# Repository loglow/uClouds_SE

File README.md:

# µClouds SE (uClouds, microClouds) Eurorack [Rev D]

## 8HP Eurorack module | Granular audio processor

[μClouds SE](http://uclouds-se.com) is a granular audio processor that creates textures and soundscapes by combining multiple segments of sound taken from a recording buffer.

This re-engineered Eurorack module updates and simplifies the classic [Mutable Instruments Clouds](https://mutable-instruments.net/modules/clouds/) design by miniaturizing the module from 18HP to 8HP and redesigning the front panel layout without eliminating any original functionality.

Fully compatible with upstream Clouds firmware. Includes power cable, mounting hardware, and a one-year warranty. Designed and built with care by [Tall Dog Electronics](http://tall-dog.com) in Western Massachusetts. Licensed [CC BY-SA 4.0](https://creativecommons.org/licenses/by-sa/4.0/) open source hardware.

- **Height:** 3U (128.5 mm)
- **Width:** 8HP (40.3 mm)
- **Depth:** 43 mm (with power)
- **+12V:** 120 mA (average)
- **-12V:** 10 mA (average)

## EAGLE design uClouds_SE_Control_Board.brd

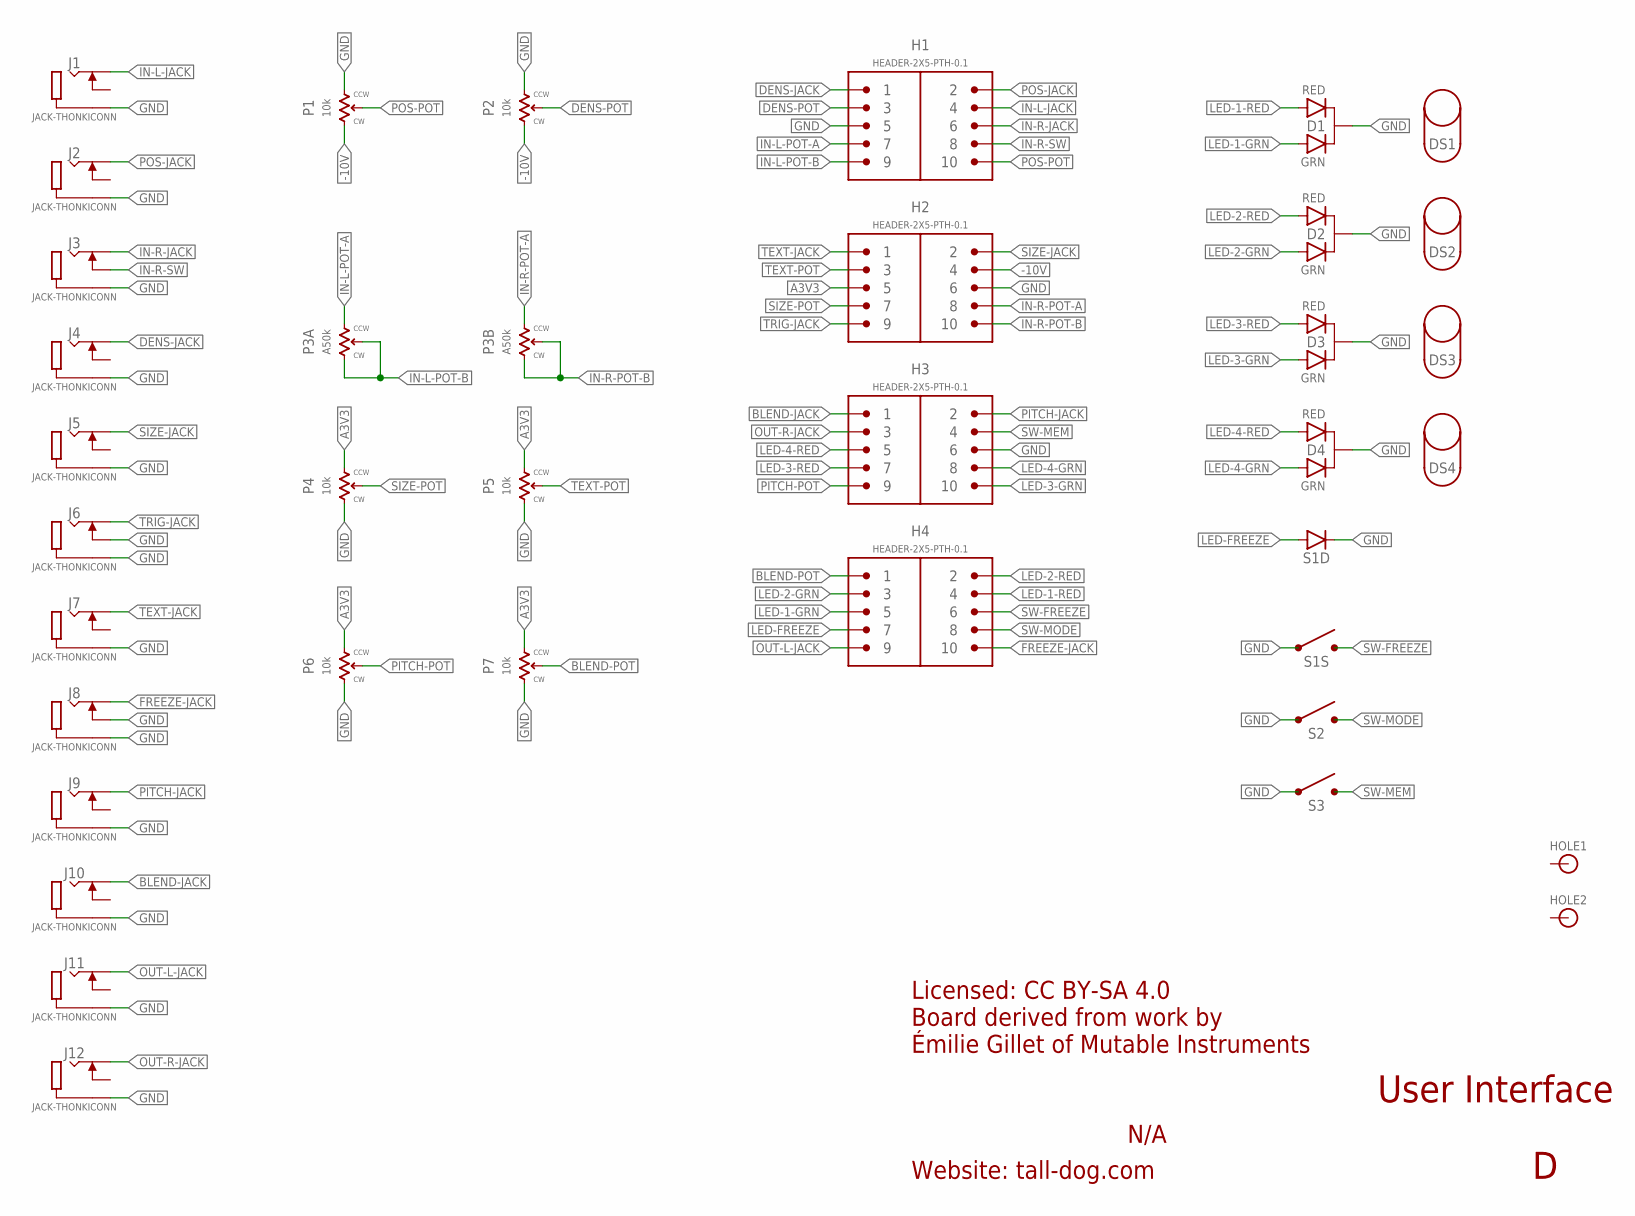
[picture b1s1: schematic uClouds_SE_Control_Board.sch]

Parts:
D1, D2, D3, D4: LED-DUAL-PTH; LED-T1-3
DS1, DS2, DS3, DS4: LED-SPACER
H1, H2, H3, H4: HEADER-2X5-PTH-0.1; PTH-0.1-2X5-MALE
HOLE1, HOLE2: HOLE; M2.5-HOLE
J1, J2, J3, J4, J5, J6, J7, J8, J9, J10, J11, J12: JACK-THONKICONN; THONKICONN
P1, P2, P4, P5, P6, P7: 10k; POT-R0904N
P3: A50k; POT-RK1109G
S1: SPST-LED; TL1265
S2, S3: SPST-PTH; TL1105

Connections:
-10V: H2.4, P1.P$3 (3), P2.P$3 (3)
A3V3: H2.5, P4.P$1 (1), P5.P$1 (1), P6.P$1 (1), P7.P$1 (1)
BLEND-JACK: H3.1, J10.P3 (3)
BLEND-POT: H4.1, P7.P$2 (2)
DENS-JACK: H1.1, J4.P3 (3)
DENS-POT: H1.3, P2.P$2 (2)
FREEZE-JACK: H4.10, J8.P3 (3)
GND: D1.2 (C), D2.2 (C), D3.2 (C), D4.2 (C), H1.5, H2.6, H3.6, J1.P1 (1), J2.P1 (1), J3.P1 (1), J4.P1 (1), J5.P1 (1), J6.P1 (1), J6.P2 (2), J7.P1 (1), J8.P1 (1), J8.P2 (2), J9.P1 (1), J10.P1 (1), J11.P1 (1), J12.P1 (1), P1.P$1 (1), P2.P$1 (1), P4.P$3 (3), P5.P$3 (3), P6.P$3 (3), P7.P$3 (3), S1.1, S1.2 (1), S1.5 (C), S2.1, S2.2 (1), S3.1, S3.2 (1)
IN-L-JACK: H1.4, J1.P3 (3)
IN-L-POT-A: H1.7, P3.1
IN-L-POT-B: H1.9, P3.2, P3.3
IN-R-JACK: H1.6, J3.P3 (3)
IN-R-POT-A: H2.8, P3.1' (1)
IN-R-POT-B: H2.10, P3.2' (2), P3.3' (3)
IN-R-SW: H1.8, J3.P2 (2)
LED-1-GRN: D1.3 (GRN), H4.5
LED-1-RED: D1.1 (RED), H4.4
LED-2-GRN: D2.3 (GRN), H4.3
LED-2-RED: D2.1 (RED), H4.2
LED-3-GRN: D3.3 (GRN), H3.10
LED-3-RED: D3.1 (RED), H3.7
LED-4-GRN: D4.3 (GRN), H3.8
LED-4-RED: D4.1 (RED), H3.5
LED-FREEZE: H4.7, S1.6 (A)
OUT-L-JACK: H4.9, J11.P3 (3)
OUT-R-JACK: H3.3, J12.P3 (3)
PITCH-JACK: H3.2, J9.P3 (3)
PITCH-POT: H3.9, P6.P$2 (2)
POS-JACK: H1.2, J2.P3 (3)
POS-POT: H1.10, P1.P$2 (2)
SIZE-JACK: H2.2, J5.P3 (3)
SIZE-POT: H2.7, P4.P$2 (2)
SW-FREEZE: H4.6, S1.3 (2), S1.4 (2)
SW-MEM: H3.4, S3.3 (2), S3.4 (2)
SW-MODE: H4.8, S2.3 (2), S2.4 (2)
TEXT-JACK: H2.1, J7.P3 (3)
TEXT-POT: H2.3, P5.P$2 (2)
TRIG-JACK: H2.9, J6.P3 (3)

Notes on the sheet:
Licensed: CC BY-SA 4.0 Board derived from work by Émilie Gillet of Mutable Instruments
Website: tall-dog.com
N/A
User Interface

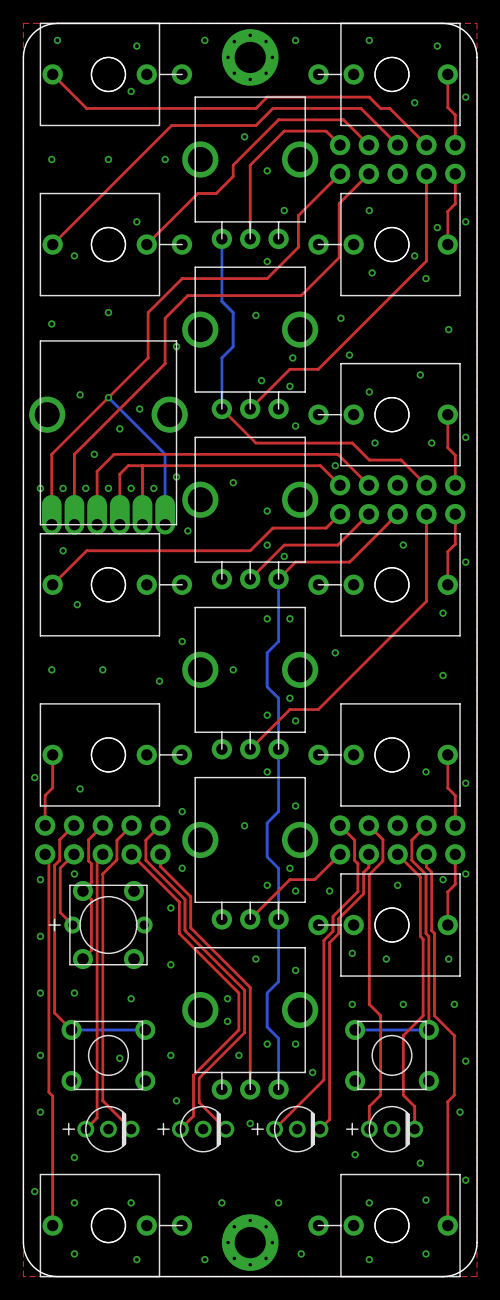
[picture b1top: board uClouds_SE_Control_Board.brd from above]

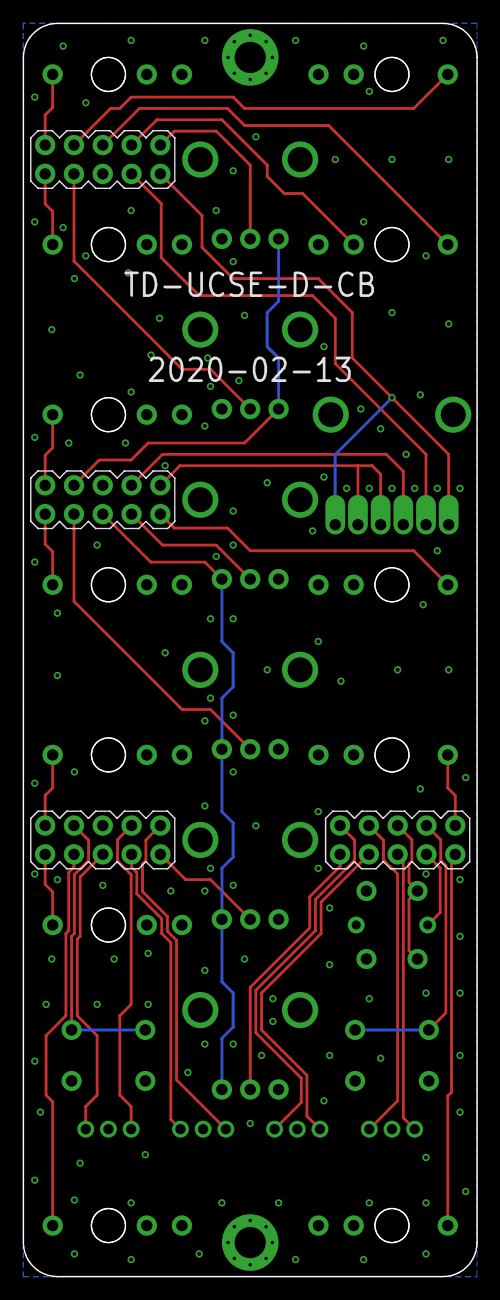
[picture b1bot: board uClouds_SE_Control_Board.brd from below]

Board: 2 copper layers, 40.0 x 110.5 mm, 36 parts (4 on the bottom side), 38 nets.

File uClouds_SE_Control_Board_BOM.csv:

Reference,Quantity,Description,Manufacturer,Part Number,Digi-Key P/N
D1 D2 D3 D4,4,LED GRN/RED DIFF 3MM ROUND T/H,Kingbright,WP3VEGW,754-1221-ND
DS1 DS2 DS3 DS4,4,LED SPACER 3MM T-1 BLACK 8MM,Essentra,LEDM-2-08,RPC4261-ND
H1 H2 H3 H4,4,CONN HEADER 10POS .100 STR 15AU,Amphenol FCI,67997-210HLF,609-3236-ND
J1 J2 J3 J4 J5 J6 J7 J8 J9 J10 J11 J12,12,3.5MM JACK VERTICAL PCB MOUNT,Wenzhou QingPu,WQP-PJ398SM,N/A
P1 P2 P4 P5 P6 P7,6,POT 9MM LINEAR B10K,Song Huei,"R0904N-B10K,L-25KQ/LWS",N/A
P3,1,POT 9MM AUDIO A50K DUAL GANG,Song Huei,"RK1109G-A50K,L-25KC",N/A
S1,1,SWITCH TACTILE SPST-NO 0.05A 12V,E-Switch,TL1265GQSCLR,EG4967-ND
S2 S3,2,SWITCH TACTILE SPST-NO 0.05A 12V,E-Switch,TL1105DF160Q,EG1865-ND

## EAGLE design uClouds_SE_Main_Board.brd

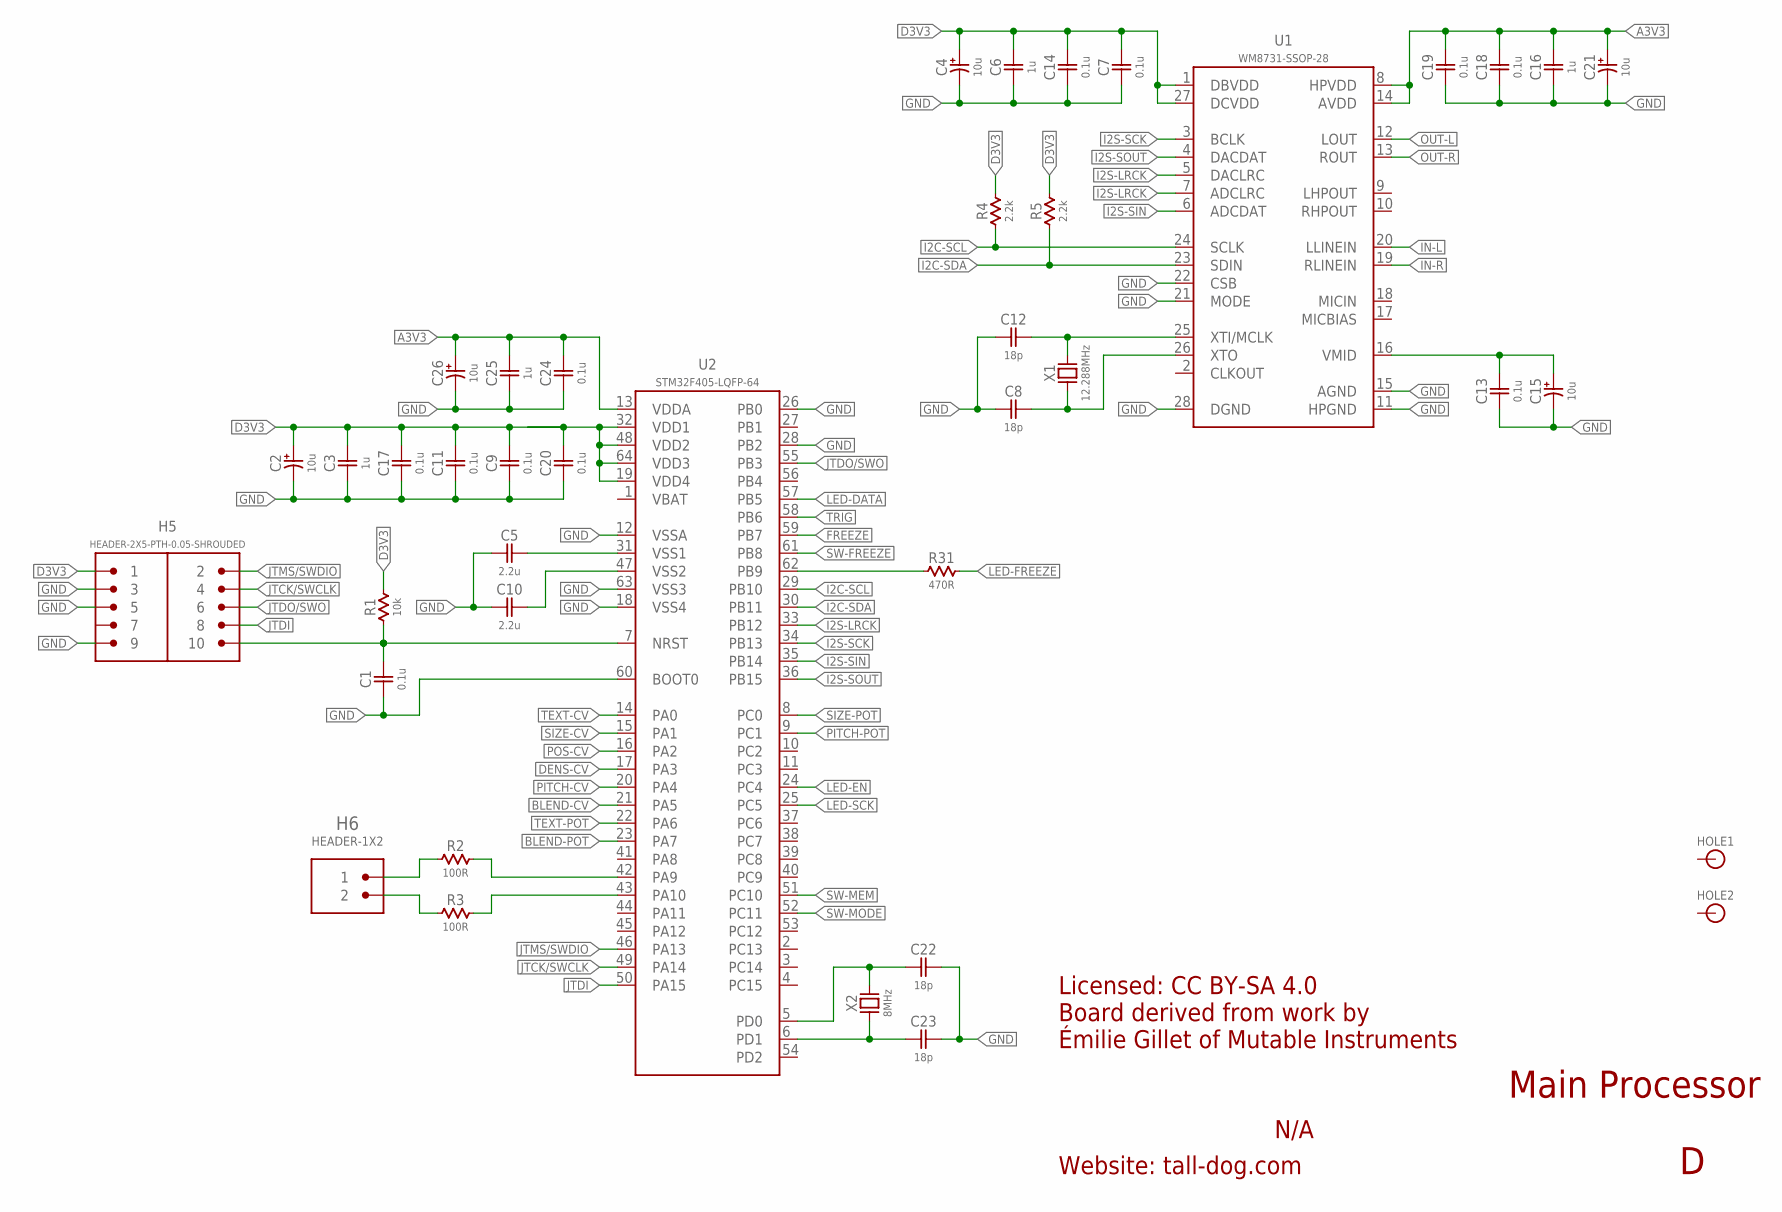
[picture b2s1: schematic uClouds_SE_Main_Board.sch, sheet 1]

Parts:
C1, C7, C9, C11, C13, C14, C17, C18, C19, C20, C24: 0.1u; 0603-NP
C2, C4, C15, C21, C26: 10u; ELECTRO-SMD-4.3MM
C3, C6, C16, C25: 1u; 0603-NP
C5, C10: 2.2u; 0603-NP
C8, C12, C22, C23: 18p; 0603-NP
H5: HEADER-2X5-PTH-0.05-SHROUDED; PTH-0.05-2X5-SHROUDED
H6: HEADER-1X2; PTH-0.1-1X2
HOLE1, HOLE2: HOLE; M2.5-HOLE
R1: 10k; 0603-NP
R2, R3: 100R; 0603-NP
R4, R5: 2.2k; 0603-NP
R31: 470R; 0603-NP
U1: WM8731-SSOP-28; SSOP-28
U2: STM32F405-LQFP-64; LQFP-64
X1: 12.288MHz; CRYSTAL-ABM3
X2: 8MHz; CRYSTAL-ABM3

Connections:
A3V3: C16.2, C18.2, C19.2, C21.A (POS), C24.2, C25.2, C26.A (POS), U1.8 (HPVDD), U1.14 (AVDD), U2.13 (VDDA); also elsewhere on the board
BLEND-CV: U2.21 (PA5); also elsewhere on the board
BLEND-POT: U2.23 (PA7); also elsewhere on the board
D3V3: C2.A (POS), C3.2, C4.A (POS), C6.2, C7.2, C9.2, C11.2, C14.2, C17.2, C20.2, H5.1, R1.2, R4.2, R5.2, U1.1 (DBVDD), U1.27 (DCVDD), U2.19 (VDD4), U2.32 (VDD1), U2.48 (VDD2), U2.64 (VDD3); also elsewhere on the board
DENS-CV: U2.17 (PA3); also elsewhere on the board
FREEZE: U2.59 (PB7); also elsewhere on the board
GND: C1.1, C2.C (NEG), C3.1, C4.C (NEG), C5.1, C6.1, C7.1, C8.1, C9.1, C10.1, C11.1, C12.1, C13.1, C14.1, C15.C (NEG), C16.1, C17.1, C18.1, C19.1, C20.1, C21.C (NEG), C22.2, C23.2, C24.1, C25.1, C26.C (NEG), H5.3, H5.5, H5.9, U1.11 (HPGND), U1.15 (AGND), U1.21 (MODE), U1.22 (CSB), U1.28 (DGND), U2.12 (VSSA), U2.18 (VSS4), U2.26 (PB0), U2.28 (PB2), U2.60 (BOOT0), U2.63 (VSS3); also elsewhere on the board
I2C-SCL: R4.1, U1.24 (SCLK), U2.29 (PB10)
I2C-SDA: R5.1, U1.23 (SDIN), U2.30 (PB11)
I2S-LRCK: U1.5 (DACLRC), U1.7 (ADCLRC), U2.33 (PB12)
I2S-SCK: U1.3 (BCLK), U2.34 (PB13)
I2S-SIN: U1.6 (ADCDAT), U2.35 (PB14)
I2S-SOUT: U1.4 (DACDAT), U2.36 (PB15)
IN-L: U1.20 (LLINEIN); also elsewhere on the board
IN-R: U1.19 (RLINEIN); also elsewhere on the board
JTCK/SWCLK: H5.4, U2.49 (PA14)
JTDI: H5.8, U2.50 (PA15)
JTDO/SWO: H5.6, U2.55 (PB3)
JTMS/SWDIO: H5.2, U2.46 (PA13)
LED-DATA: U2.57 (PB5); also elsewhere on the board
LED-EN: U2.24 (PC4); also elsewhere on the board
LED-FREEZE: R31.2; also elsewhere on the board
LED-SCK: U2.25 (PC5); also elsewhere on the board
unnamed: C5.2, U2.31 (VSS1)
unnamed: C10.2, U2.47 (VSS2)
unnamed: C22.1, U2.5 (PD0), X2.2
unnamed: C23.1, U2.6 (PD1), X2.1
unnamed: C12.2, U1.25 (XTI/MCLK), X1.2
unnamed: C8.2, U1.26 (XTO), X1.1
unnamed: C13.2, C15.A (POS), U1.16 (VMID)
unnamed: R31.1, U2.62 (PB9)
OUT-L: U1.12 (LOUT); also elsewhere on the board
OUT-R: U1.13 (ROUT); also elsewhere on the board
PITCH-CV: U2.20 (PA4); also elsewhere on the board
PITCH-POT: U2.9 (PC1); also elsewhere on the board
POS-CV: U2.16 (PA2); also elsewhere on the board
RESET: C1.2, H5.10, R1.1, U2.7 (NRST)
RX: H6.2, R3.1
RX1: R3.2, U2.43 (PA10)
SIZE-CV: U2.15 (PA1); also elsewhere on the board
SIZE-POT: U2.8 (PC0); also elsewhere on the board
SW-FREEZE: U2.61 (PB8); also elsewhere on the board
SW-MEM: U2.51 (PC10); also elsewhere on the board
SW-MODE: U2.52 (PC11); also elsewhere on the board
TEXT-CV: U2.14 (PA0); also elsewhere on the board
TEXT-POT: U2.22 (PA6); also elsewhere on the board
TRIG: U2.58 (PB6); also elsewhere on the board
TX: H6.1, R2.1
TX1: R2.2, U2.42 (PA9)

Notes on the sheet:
Licensed: CC BY-SA 4.0 Board derived from work by Émilie Gillet of Mutable Instruments
Website: tall-dog.com
N/A
Main Processor

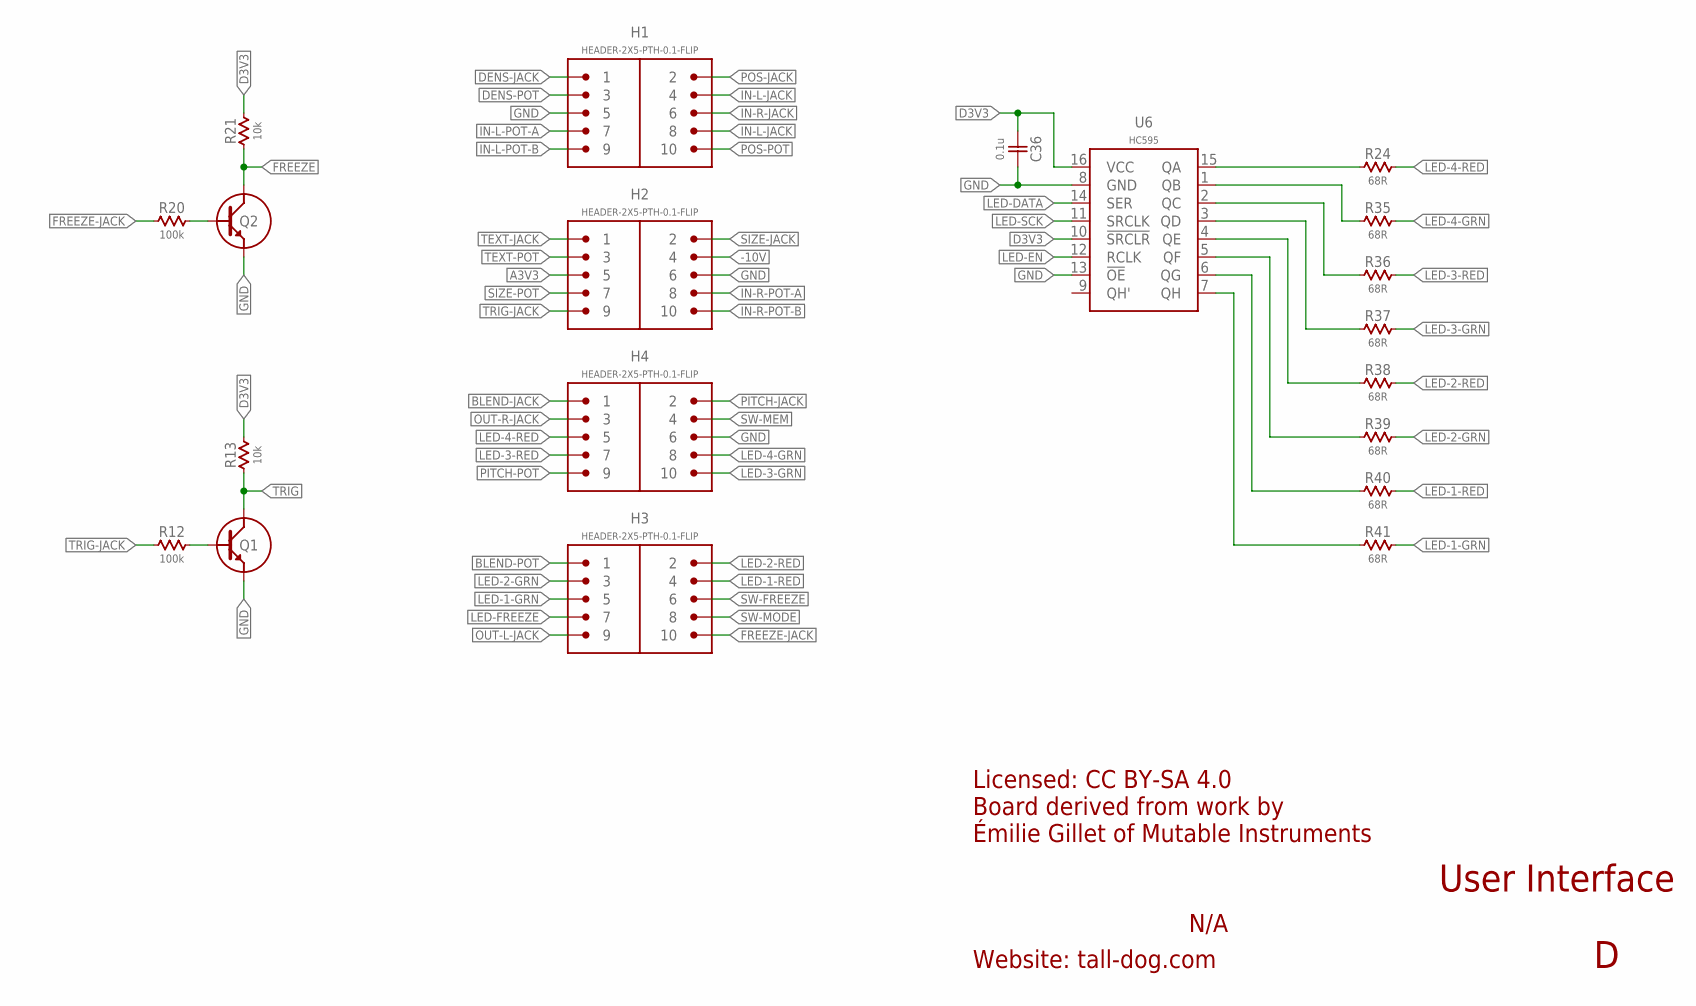
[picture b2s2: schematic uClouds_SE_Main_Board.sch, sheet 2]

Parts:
C36: 0.1u; 0603-NP
H1, H2, H3, H4: HEADER-2X5-PTH-0.1-FLIP; PTH-0.1-2X5-FEMALE
Q1, Q2: NPN-SOT23-BEC; SOT-23
R12, R20: 100k; 0603-NP
R13, R21: 10k; 0603-NP
R24, R35, R36, R37, R38, R39, R40, R41: 68R; 0603-NP
U6: HC595; TSSOP-16

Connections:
-10V: H2.4; also elsewhere on the board
A3V3: H2.5; also elsewhere on the board
BLEND-JACK: H4.1; also elsewhere on the board
BLEND-POT: H3.1; also elsewhere on the board
D3V3: C36.2, R13.2, R21.2, U6.10 (!SRCLR), U6.16 (VCC); also elsewhere on the board
DENS-JACK: H1.1; also elsewhere on the board
DENS-POT: H1.3; also elsewhere on the board
FREEZE: Q2.3 (C), R21.1; also elsewhere on the board
FREEZE-JACK: H3.10, R20.1
GND: C36.1, H1.5, H2.6, H4.6, Q1.2 (E), Q2.2 (E), U6.8 (GND), U6.13 (!OE); also elsewhere on the board
IN-L-JACK: H1.4, H1.8; also elsewhere on the board
IN-L-POT-A: H1.7; also elsewhere on the board
IN-L-POT-B: H1.9; also elsewhere on the board
IN-R-JACK: H1.6; also elsewhere on the board
IN-R-POT-A: H2.8; also elsewhere on the board
IN-R-POT-B: H2.10; also elsewhere on the board
LED-1-GRN: H3.5, R41.2
LED-1-RED: H3.4, R40.2
LED-2-GRN: H3.3, R39.2
LED-2-RED: H3.2, R38.2
LED-3-GRN: H4.10, R37.2
LED-3-RED: H4.7, R36.2
LED-4-GRN: H4.8, R35.2
LED-4-RED: H4.5, R24.2
LED-DATA: U6.14 (SER); also elsewhere on the board
LED-EN: U6.12 (RCLK); also elsewhere on the board
LED-FREEZE: H3.7; also elsewhere on the board
LED-SCK: U6.11 (SRCLK); also elsewhere on the board
unnamed: R24.1, U6.15 (QA)
unnamed: R35.1, U6.1 (QB)
unnamed: R36.1, U6.2 (QC)
unnamed: Q1.1 (B), R12.2
unnamed: Q2.1 (B), R20.2
unnamed: R37.1, U6.3 (QD)
unnamed: R38.1, U6.4 (QE)
unnamed: R39.1, U6.5 (QF)
unnamed: R40.1, U6.6 (QG)
unnamed: R41.1, U6.7 (QH)
OUT-L-JACK: H3.9; also elsewhere on the board
OUT-R-JACK: H4.3; also elsewhere on the board
PITCH-JACK: H4.2; also elsewhere on the board
PITCH-POT: H4.9; also elsewhere on the board
POS-JACK: H1.2; also elsewhere on the board
POS-POT: H1.10; also elsewhere on the board
SIZE-JACK: H2.2; also elsewhere on the board
SIZE-POT: H2.7; also elsewhere on the board
SW-FREEZE: H3.6; also elsewhere on the board
SW-MEM: H4.4; also elsewhere on the board
SW-MODE: H3.8; also elsewhere on the board
TEXT-JACK: H2.1; also elsewhere on the board
TEXT-POT: H2.3; also elsewhere on the board
TRIG: Q1.3 (C), R13.1; also elsewhere on the board
TRIG-JACK: H2.9, R12.1

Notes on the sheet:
Licensed: CC BY-SA 4.0 Board derived from work by Émilie Gillet of Mutable Instruments
Website: tall-dog.com
N/A
User Interface

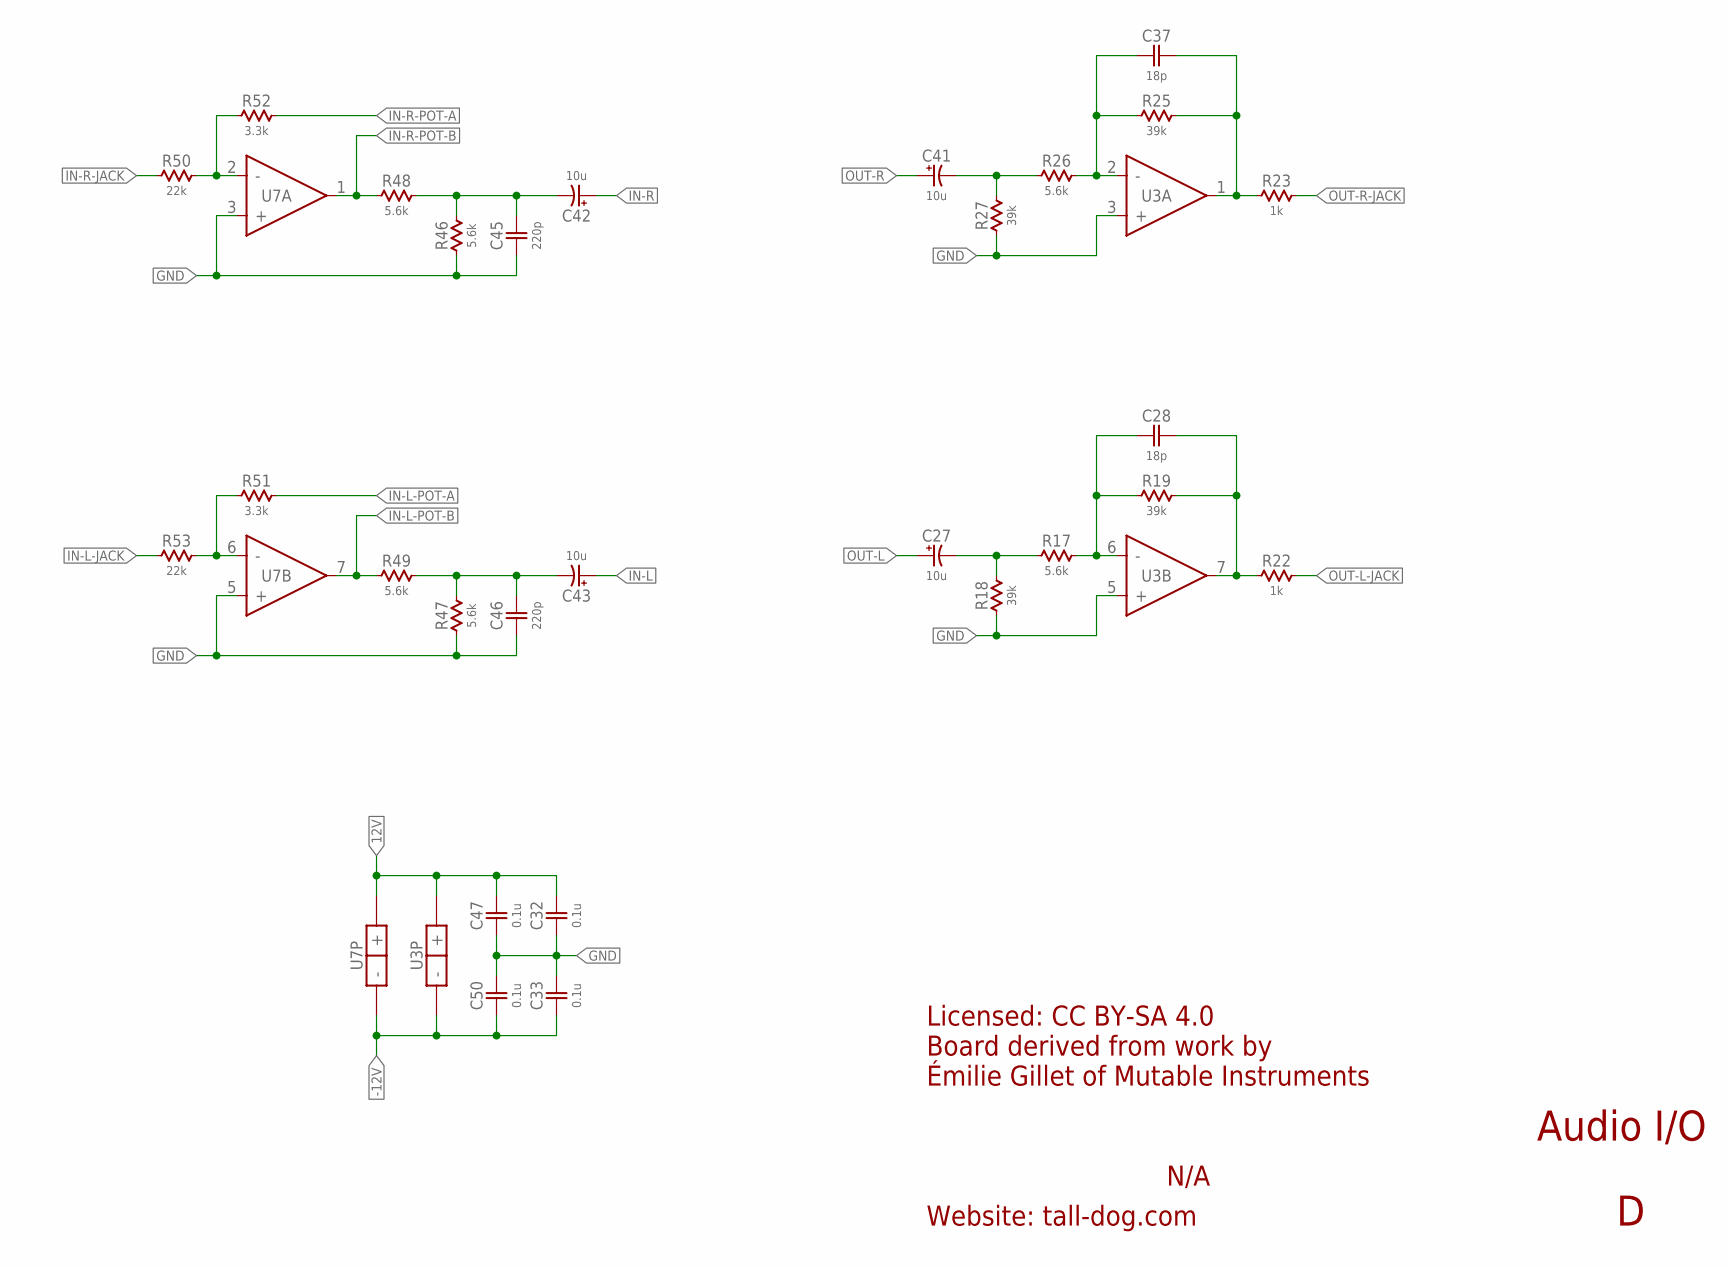
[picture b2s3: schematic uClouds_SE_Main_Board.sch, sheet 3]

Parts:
C27, C41, C42, C43: 10u; ELECTRO-SMD-4.3MM
C28, C37: 18p; 0603-NP
C32, C33, C47, C50: 0.1u; 0603-NP
C45, C46: 220p; 0603-NP
R17, R26, R46, R47, R48, R49: 5.6k; 0603-NP
R18, R19, R25, R27: 39k; 0603-NP
R22, R23: 1k; 0603-NP
R50, R53: 22k; 0603-NP
R51, R52: 3.3k; 0603-NP
U3, U7: TL072-TSSOP-8; TSSOP-8

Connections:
12V: C32.2, C47.2, U3.8 (+), U7.8 (+); also elsewhere on the board
-12V: C33.1, C50.1, U3.4 (-), U7.4 (-); also elsewhere on the board
GND: C32.1, C33.2, C45.1, C46.1, C47.1, C50.2, R18.1, R27.1, R46.1, R47.1, U3.3 (+), U3.5 (+), U7.3 (+), U7.5 (+); also elsewhere on the board
IN-L: C43.A (POS); also elsewhere on the board
IN-L-JACK: R53.1; also elsewhere on the board
IN-L-POT-A: R51.2; also elsewhere on the board
IN-L-POT-B: R49.1, U7.7 (OUT); also elsewhere on the board
IN-R: C42.A (POS); also elsewhere on the board
IN-R-JACK: R50.1; also elsewhere on the board
IN-R-POT-A: R52.2; also elsewhere on the board
IN-R-POT-B: R48.1, U7.1 (OUT); also elsewhere on the board
unnamed: R50.2, R52.1, U7.2 (-)
unnamed: R51.1, R53.2, U7.6 (-)
unnamed: C27.C (NEG), R17.1, R18.2
unnamed: C43.C (NEG), C46.2, R47.2, R49.2
unnamed: C41.C (NEG), R26.1, R27.2
unnamed: C28.1, R17.2, R19.1, U3.6 (-)
unnamed: C28.2, R19.2, R22.1, U3.7 (OUT)
unnamed: C37.1, R25.1, R26.2, U3.2 (-)
unnamed: C37.2, R23.1, R25.2, U3.1 (OUT)
unnamed: C42.C (NEG), C45.2, R46.2, R48.2
OUT-L: C27.A (POS); also elsewhere on the board
OUT-L-JACK: R22.2; also elsewhere on the board
OUT-R: C41.A (POS); also elsewhere on the board
OUT-R-JACK: R23.2; also elsewhere on the board

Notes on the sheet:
Licensed: CC BY-SA 4.0 Board derived from work by Émilie Gillet of Mutable Instruments
Website: tall-dog.com
N/A
Audio I/O

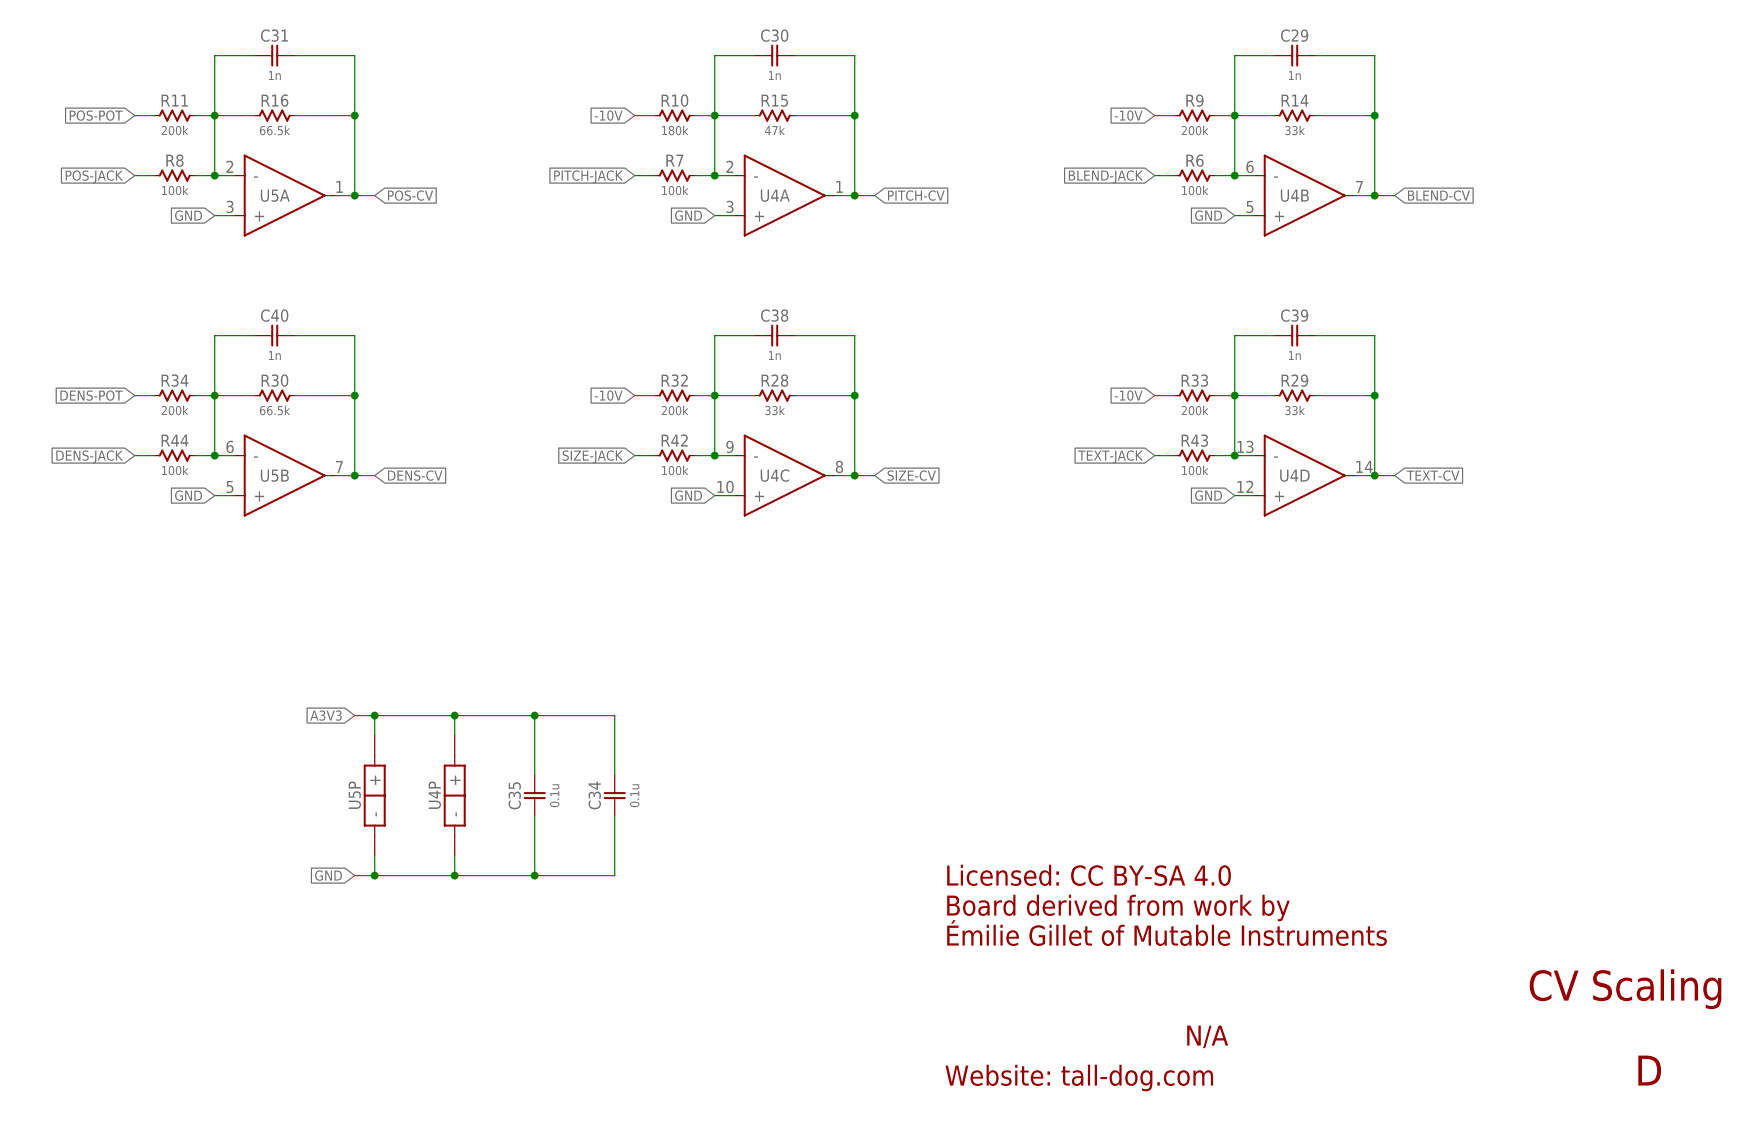
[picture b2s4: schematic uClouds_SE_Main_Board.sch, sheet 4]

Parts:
C29, C30, C31, C38, C39, C40: 1n; 0603-NP
C34, C35: 0.1u; 0603-NP
R6, R7, R8, R42, R43, R44: 100k; 0603-NP
R9, R11, R32, R33, R34: 200k; 0603-NP
R10: 180k; 0603-NP
R14, R28, R29: 33k; 0603-NP
R15: 47k; 0603-NP
R16, R30: 66.5k; 0603-NP
U4: MCP6004-TSSOP-14; TSSOP-14
U5: MCP6002-MSOP-8; MSOP-8

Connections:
-10V: R9.1, R10.1, R32.1, R33.1; also elsewhere on the board
A3V3: C34.2, C35.2, U4.4 (+), U5.8 (+); also elsewhere on the board
BLEND-CV: C29.2, R14.2, U4.7 (OUT); also elsewhere on the board
BLEND-JACK: R6.1; also elsewhere on the board
DENS-CV: C40.2, R30.2, U5.7 (OUT); also elsewhere on the board
DENS-JACK: R44.1; also elsewhere on the board
DENS-POT: R34.1; also elsewhere on the board
GND: C34.1, C35.1, U4.3 (+), U4.5 (+), U4.10 (+), U4.11 (-), U4.12 (+), U5.3 (+), U5.4 (-), U5.5 (+); also elsewhere on the board
unnamed: C29.1, R6.2, R9.2, R14.1, U4.6 (-)
unnamed: C31.1, R8.2, R11.2, R16.1, U5.2 (-)
unnamed: C40.1, R30.1, R34.2, R44.2, U5.6 (-)
unnamed: C38.1, R28.1, R32.2, R42.2, U4.9 (-)
unnamed: C30.1, R7.2, R10.2, R15.1, U4.2 (-)
unnamed: C39.1, R29.1, R33.2, R43.2, U4.13 (-)
PITCH-CV: C30.2, R15.2, U4.1 (OUT); also elsewhere on the board
PITCH-JACK: R7.1; also elsewhere on the board
POS-CV: C31.2, R16.2, U5.1 (OUT); also elsewhere on the board
POS-JACK: R8.1; also elsewhere on the board
POS-POT: R11.1; also elsewhere on the board
SIZE-CV: C38.2, R28.2, U4.8 (OUT); also elsewhere on the board
SIZE-JACK: R42.1; also elsewhere on the board
TEXT-CV: C39.2, R29.2, U4.14 (OUT); also elsewhere on the board
TEXT-JACK: R43.1; also elsewhere on the board

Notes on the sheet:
Licensed: CC BY-SA 4.0 Board derived from work by Émilie Gillet of Mutable Instruments
Website: tall-dog.com
N/A
CV Scaling

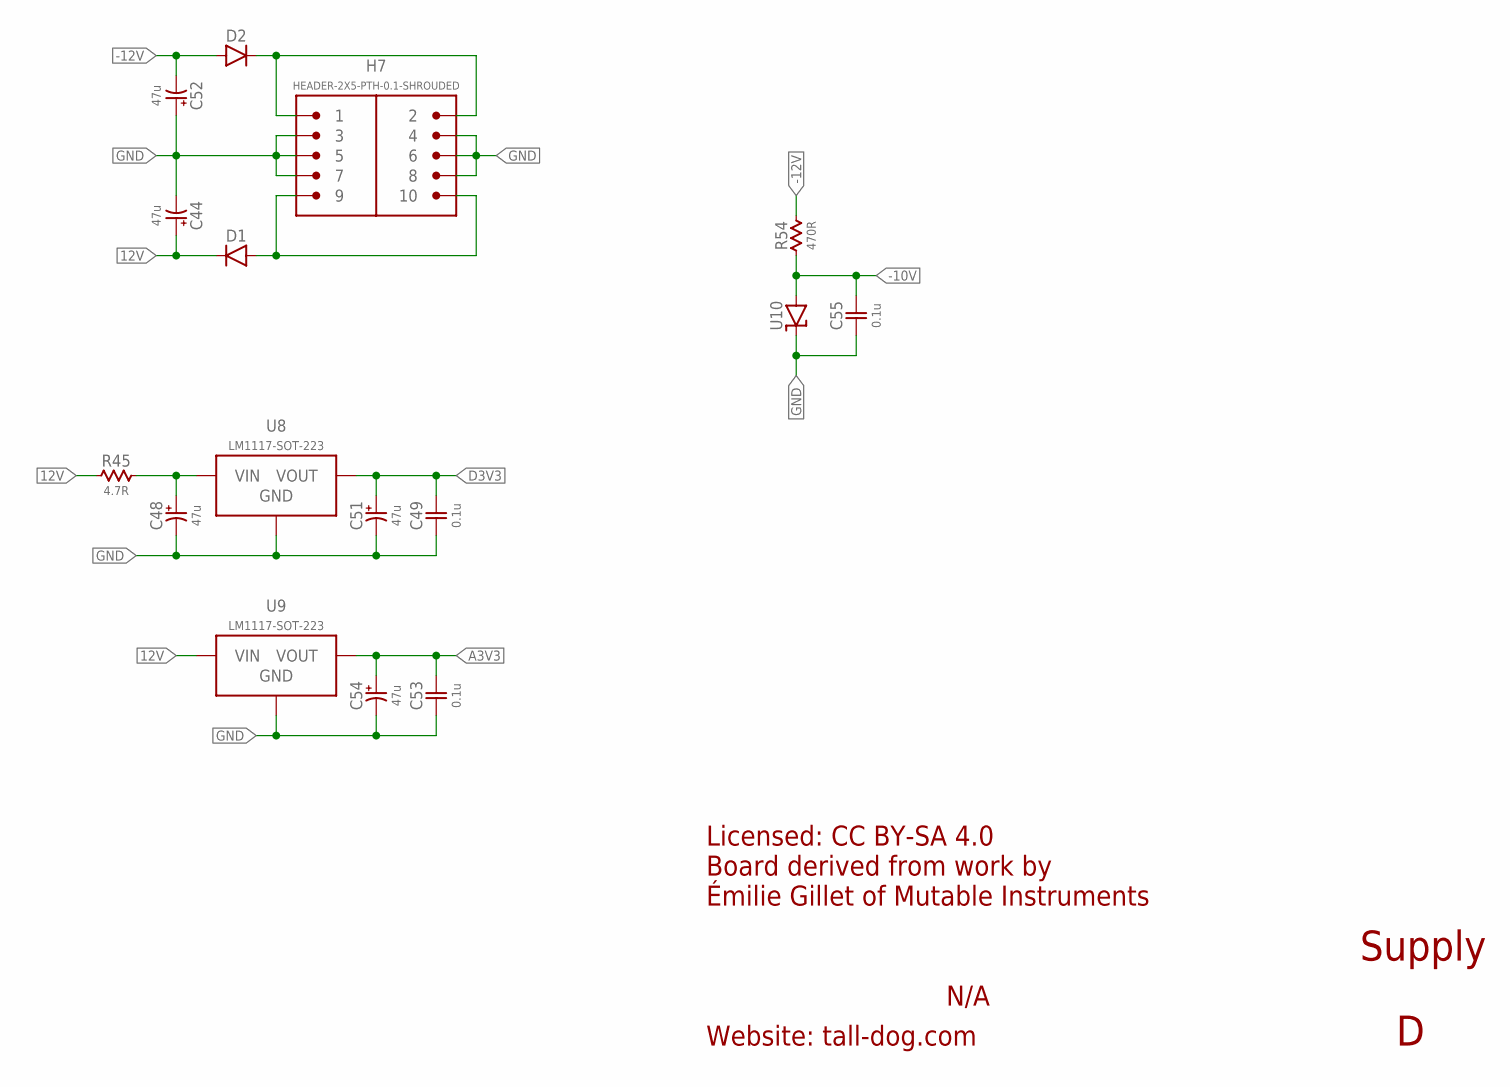
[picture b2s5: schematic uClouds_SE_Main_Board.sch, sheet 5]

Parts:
C44, C48, C51, C52, C54: 47u; ELECTRO-SMD-6.6MM
C49, C53, C55: 0.1u; 0603-NP
D1, D2: DIODE-SOD123; SOD-123
H7: HEADER-2X5-PTH-0.1-SHROUDED; PTH-0.1-2X5-SHROUDED
R45: 4.7R; 1206-NP
R54: 470R; 0603-NP
U8, U9: LM1117-SOT-223; SOT-223
U10: ZENER-SOT-23; SOT-23

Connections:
12V: C44.A (POS), D1.C, R45.1, U9.3 (VIN); also elsewhere on the board
-10V: C55.2, R54.1, U10.2 (A); also elsewhere on the board
-12V: C52.C (NEG), D2.A, R54.2; also elsewhere on the board
A3V3: C53.2, C54.A (POS), U9.2 (VOUT), U9.4 (VOUT); also elsewhere on the board
D3V3: C49.2, C51.A (POS), U8.2 (VOUT), U8.4 (VOUT); also elsewhere on the board
GND: C44.C (NEG), C48.C (NEG), C49.1, C51.C (NEG), C52.A (POS), C53.1, C54.C (NEG), C55.1, H7.3, H7.4, H7.5, H7.6, H7.7, H7.8, U8.1 (GND), U9.1 (GND), U10.1 (C); also elsewhere on the board
unnamed: C48.A (POS), R45.2, U8.3 (VIN)
unnamed: D2.C, H7.1, H7.2
unnamed: D1.A, H7.9, H7.10

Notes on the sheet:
Licensed: CC BY-SA 4.0 Board derived from work by Émilie Gillet of Mutable Instruments
Website: tall-dog.com
N/A
Supply

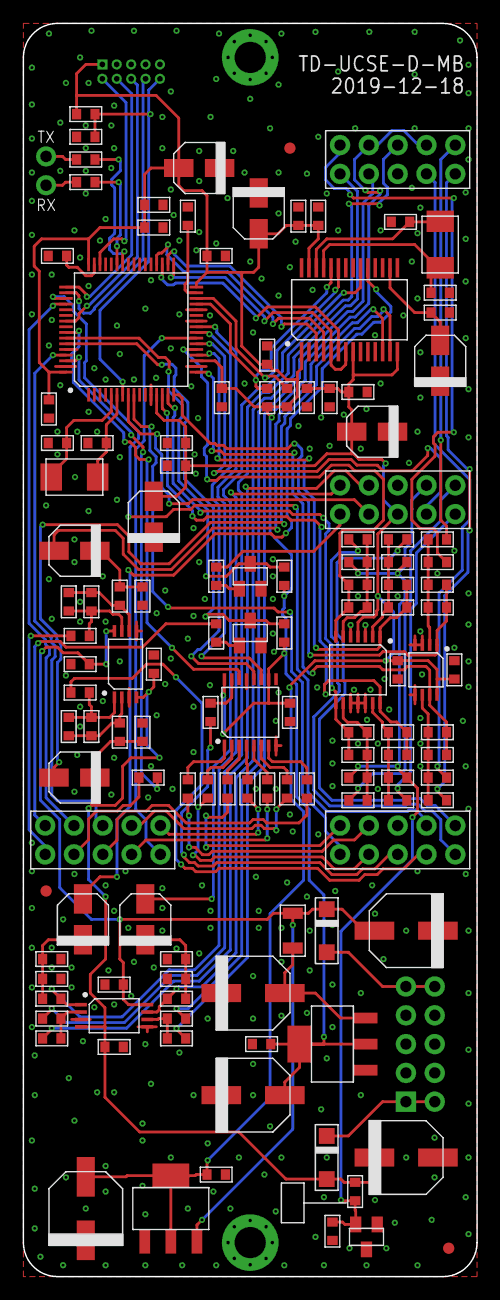
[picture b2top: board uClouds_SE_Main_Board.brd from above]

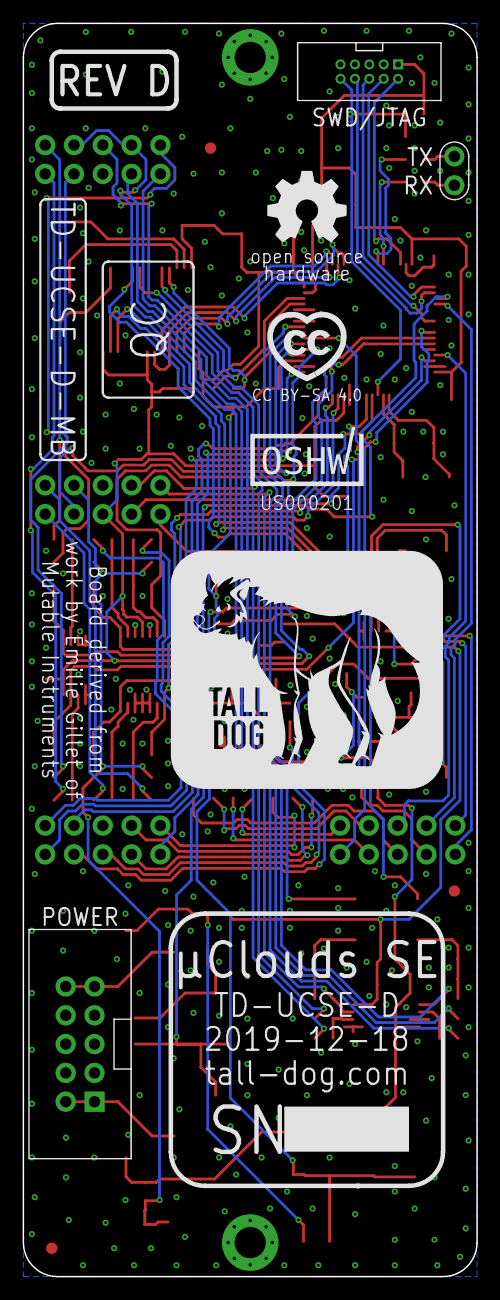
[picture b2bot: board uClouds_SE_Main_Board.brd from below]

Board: 2 copper layers, 40.0 x 110.5 mm, 145 parts (15 on the bottom side), 107 nets.

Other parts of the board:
U$1, U$3, U$6: FIDUCIAL
U$2: LOGO-OSHW
U$4: LOGO-OSH
U$5: LOGO-CC
U$7: LOGO-REV
U$8: LOGO-SN
U$9: LOGO-TD
U$10: LOGO-PN
U$11: LOGO-QC

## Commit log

2018-11-17 initial commit, revision C production
2019-07-12 assembly process updates
2019-12-14 Updates for Revision D
2019-12-18 Cleanup and silkscreen artwork updates
2021-03-23 Revision D
